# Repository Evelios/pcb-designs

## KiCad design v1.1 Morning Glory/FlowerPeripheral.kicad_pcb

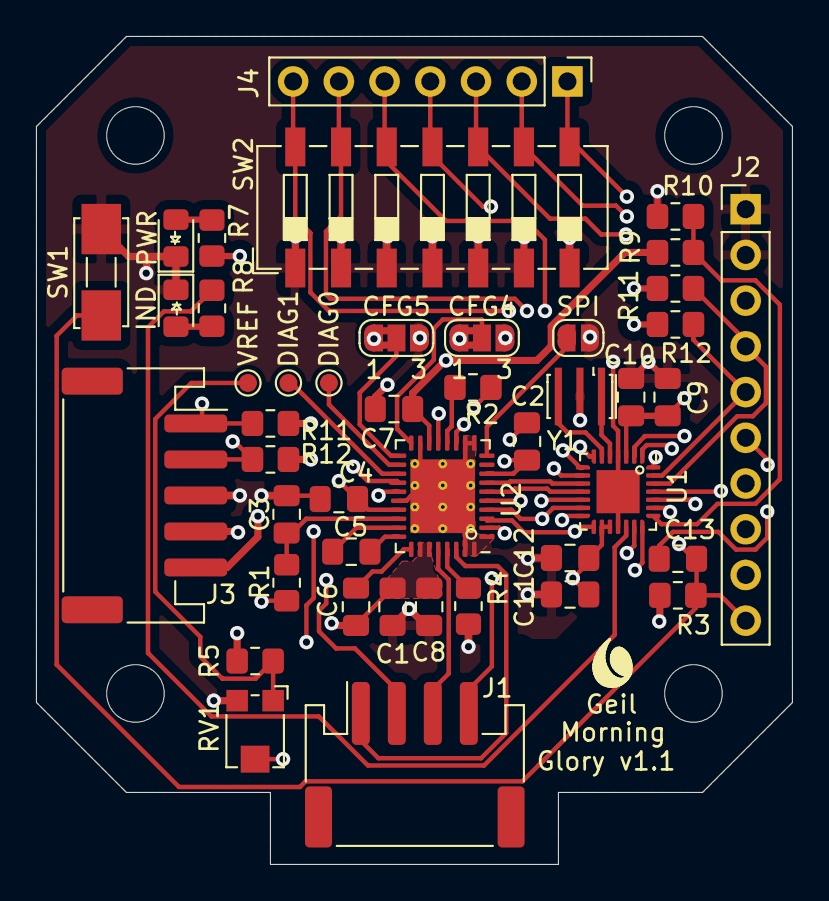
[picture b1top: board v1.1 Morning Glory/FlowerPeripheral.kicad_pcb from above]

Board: 4 copper layers, 42.0 x 46.0 mm, 45 parts (0 on the bottom side), 46 nets.

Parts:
C1, C2, C6, C7, C10, C11: 100n/50V; C_0805_2012Metric_Pad1.18x1.45mm_HandSolder
C3: 470n/10V; C_0805_2012Metric_Pad1.18x1.45mm_HandSolder
C4: 4u7/10v; C_0805_2012Metric_Pad1.18x1.45mm_HandSolder
C5: 22n/50V; C_0805_2012Metric_Pad1.18x1.45mm_HandSolder
C8: 1u/50V; C_0805_2012Metric_Pad1.18x1.45mm_HandSolder
C9: 10u; C_0805_2012Metric_Pad1.18x1.45mm_HandSolder
C12: 0.1u; C_0805_2012Metric_Pad1.18x1.45mm_HandSolder
C13: 100nF/50V; C_0805_2012Metric_Pad1.18x1.45mm_HandSolder
D2: PWR; LED_0805_2012Metric_Pad1.15x1.40mm_HandSolder_WithDirection
D3: IND; LED_0805_2012Metric_Pad1.15x1.40mm_HandSolder_WithDirection
H1: Nema17; Nema 17
J1: Motor Connector; JST_PH_S4B-PH-SM4-TB_1x04-1MP_P2.00mm_Horizontal
J2: Male Connector 10 Pin; PinHeader_1x10_P2.54mm_Vertical
J3: JST 5 Pin; JST_PH_S5B-PH-SM4-TB_1x05-1MP_P2.00mm_Horizontal
J4: Conn_01x07; PinHeader_1x07_P2.54mm_Vertical
J5: DIAG0; TestPoint_Pad_D1.0mm
J6: DIAG1; TestPoint_Pad_D1.0mm
J7: VREF; TestPoint_Pad_D1.0mm
JP1: SPI; SolderJumper-2_P1.3mm_Open_RoundedPad1.0x1.5mm
JP2: CFG4; SolderJumper-3_P1.3mm_Bridged2Bar12_RoundedPad1.0x1.5mm_Num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
JP3: CFG5; SolderJumper-3_P1.3mm_Bridged2Bar12_RoundedPad1.0x1.5mm_Num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
R1: 2R2; R_0805_2012Metric_Pad1.20x1.40mm_HandSolder
R2, R4: R0805/0R11; R_0805_2012Metric_Pad1.20x1.40mm_HandSolder
R3, R11, R11#2, R12, R12#2: 10K; R_0805_2012Metric_Pad1.20x1.40mm_HandSolder
R5: 20K; R_0805_2012Metric_Pad1.20x1.40mm_HandSolder
R7, R8: 150Ω; R_0805_2012Metric_Pad1.20x1.40mm_HandSolder
R9: 1M; R_0805_2012Metric_Pad1.20x1.40mm_HandSolder
R10: 100K; R_0805_2012Metric_Pad1.20x1.40mm_HandSolder
RV1: 20K; Potentiometer_Bourns_TC33X_Vertical
SW1: SW_SPST; SPST_FSM2JMTR
SW2: SW_DIP_x07; SW_DIP_SPSTx07_Slide_6.7x19.34mm_W6.73mm_P2.54mm_LowProfile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
U1: ATmega328P-PU; QFN-28-1EP_4x4mm_P0.45mm_EP2.4x2.4mm
U2: TMC2130-LA; QFN-36-1EP_5x6mm_P0.5mm_EP3.6x4.1mm_ThermalVias
Y1: 16Mhz; Resonator_SMD_muRata_CSTxExxV-3Pin_3.0x1.1mm_HandSoldering

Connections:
+5V: C2.1, C4.2, C9.1, C10.1, C11.1, C12.1, J2.3, J3.4, JP2.3, JP3.1, R1.1, R3.2, R5.2, R7.1, R11.1, R11#2.1, R12.1, R12#2.1, U1.3, U1.16, U1.17, U2.8, U2.25
+12V: C1.1, C6.1, C7.1, C8.1, J3.5, R9.1, U2.16, U2.30, U2.31
/CLKA: U1.5, Y1.1
/CLKB: U1.6, Y1.3
/DIR: U1.10, U2.7
/IND: R8.1, U1.19
/MISO: J2.8, U1.14, U2.5
/MOSI: J2.9, U1.13, U2.4
/P1: J4.7, SW2.14, U1.28
/P2: J4.6, SW2.13, U1.1
/P3: J4.5, SW2.12, U1.2
/P4: J4.4, SW2.11, U1.7
/P5: J4.3, SW2.10, U1.8
/P6: J4.2, SW2.9, U1.20
/P7: J4.1, SW2.8, U1.21
/RESET: C13.2, J2.10, R3.1, SW1.2, U1.25
/RX: J2.4, R11#2.2, U1.26
/SCK: J2.7, U1.15, U2.3
/SCL: J3.2, R12.2, U1.24
/SDA: J3.1, R11.2, U1.23
/SS: U1.12, U2.2
/STEP: U1.11, U2.6
/TMC2130_silentstepstick_v11/CFG4: JP2.2, U2.18
/TMC2130_silentstepstick_v11/CFG5: JP3.2, U2.19
/TMC2130_silentstepstick_v11/EN: U1.9, U2.22
/TMC2130_silentstepstick_v11/MA1: J1.1, U2.34
/TMC2130_silentstepstick_v11/MA2: J1.3, U2.32
/TMC2130_silentstepstick_v11/MB1: J1.4, U2.13
/TMC2130_silentstepstick_v11/MB2: J1.2, U2.15
/TX: J2.5, R12#2.2, U1.27
/VM_REF: R9.2, R10.1, U1.22
GND: C1.2, C2.2, C3.1, C4.1, C7.2, C8.2, C9.2, C10.2, C11.2, C12.2, D2.1, D3.1, J2.1, J2.2, J3.3, JP1.1, JP2.1, JP3.3, R2.2, R4.2, R10.2, RV1.3, SW1.1, SW2.1, SW2.2, SW2.3, SW2.4, SW2.5, SW2.6, SW2.7, U1.4, U1.18, U1.29, U2.1, U2.11, U2.12, U2.17, U2.24, U2.35, U2.36, U2.37, Y1.2
unnamed: C3.2, R1.2, U2.26
unnamed: C5.1, U2.28
unnamed: C5.2, U2.27
unnamed: C6.2, U2.29
unnamed: C13.1, J2.6
unnamed: D2.2, R7.2
unnamed: D3.2, R8.2
unnamed: J5.1, U2.20
unnamed: J6.1, U2.21
unnamed: J7.1, R5.1, RV1.1
unnamed: JP1.2, U2.10
unnamed: R2.1, U2.14
unnamed: R4.1, U2.33
unnamed: RV1.2, U2.23

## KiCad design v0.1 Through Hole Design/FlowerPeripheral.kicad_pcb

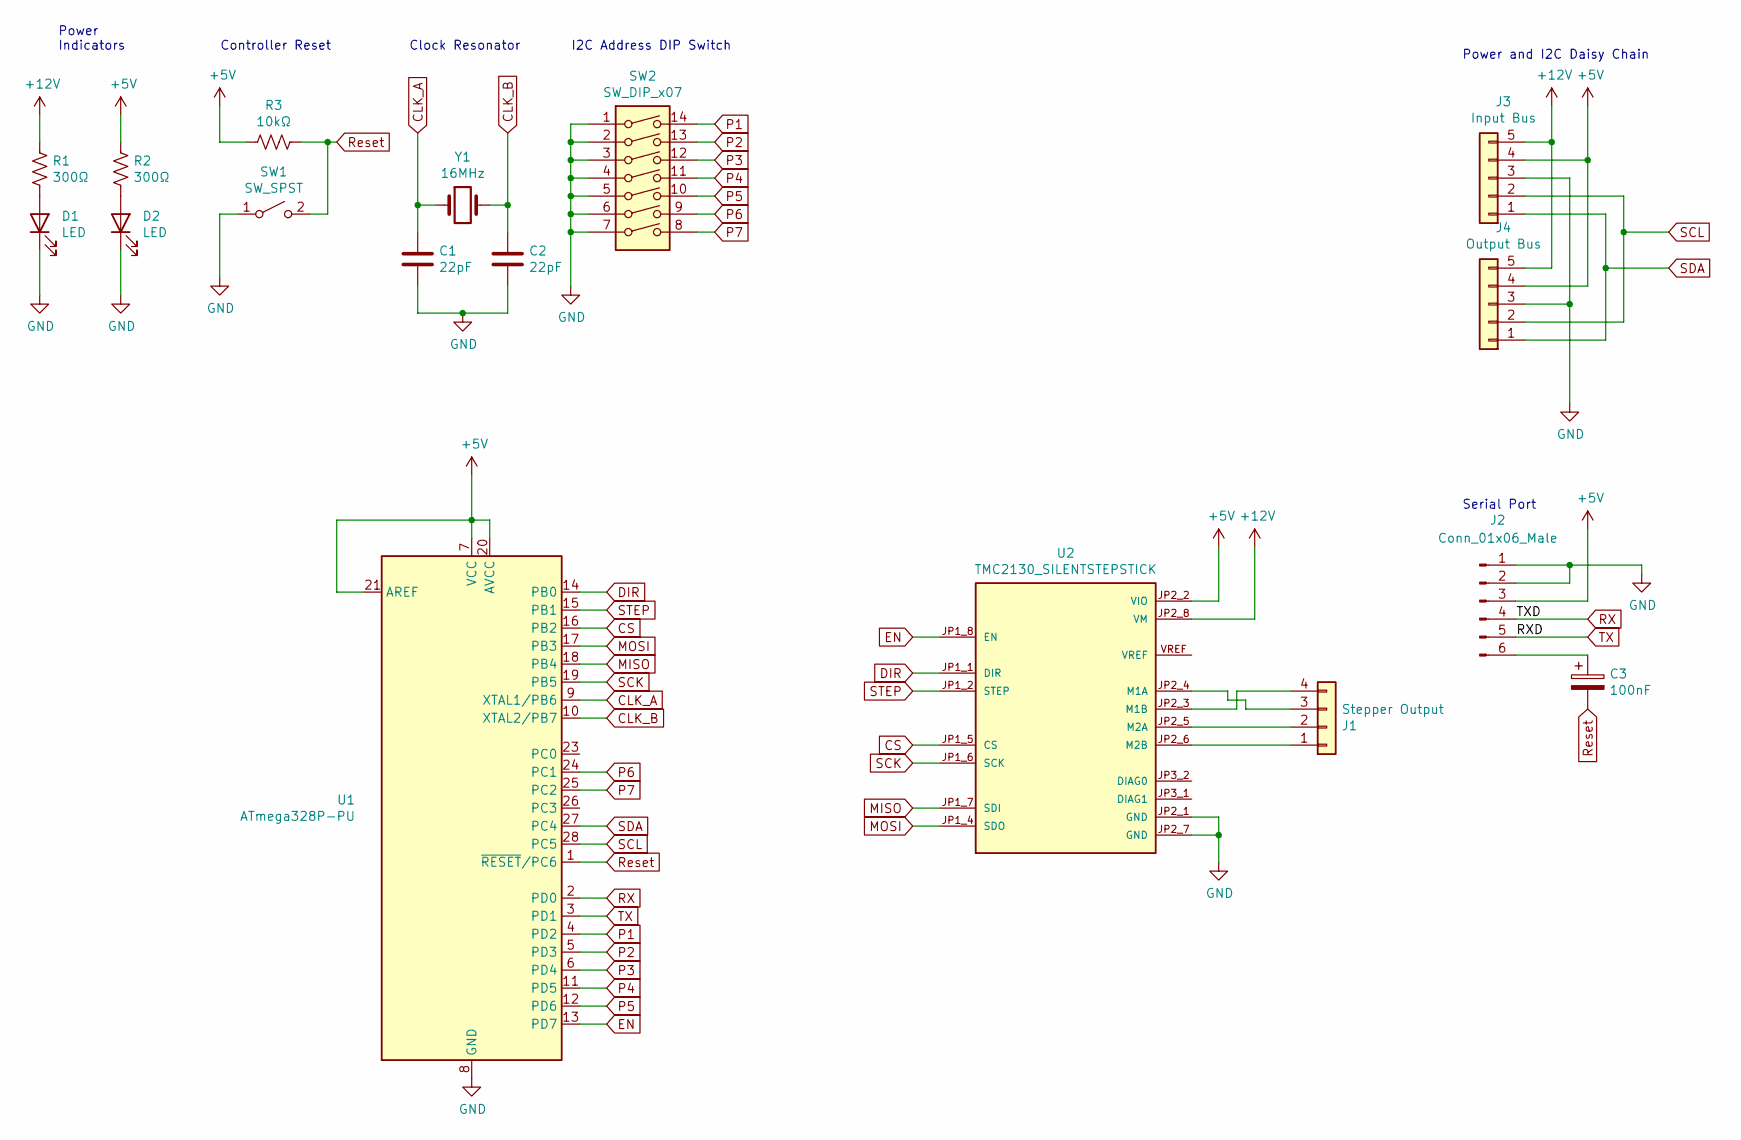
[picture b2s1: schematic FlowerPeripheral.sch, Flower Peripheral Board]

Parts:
C1, C2: 22pF; C_Disc_D5.0mm_W2.5mm_P2.50mm
C3: 100nF; CP_Radial_D4.0mm_P1.50mm
D1, D2: LED; LED_D3.0mm
J1: Stepper Output; JST_XH_B4B-XH-A_1x04_P2.50mm_Vertical
J2: Conn_01x06_Male; PinHeader_1x06_P2.54mm_Vertical
J3: Input Bus; JST_XH_B5B-XH-A_1x05_P2.50mm_Vertical
J4: Output Bus; JST_XH_B5B-XH-A_1x05_P2.50mm_Vertical
R1, R2: 300Ω; R_Axial_DIN0207_L6.3mm_D2.5mm_P10.16mm_Horizontal
R3: 10kΩ; R_Axial_DIN0207_L6.3mm_D2.5mm_P10.16mm_Horizontal
SW1: SW_SPST; SW_PUSH_6mm_H5mm
SW2: SW_DIP_x07; SW_DIP_SPSTx07_Slide_9.78x19.96mm_W7.62mm_P2.54mm
U1: ATmega328P-PU; DIP-28_W7.62mm_Socket
U2: TMC2130_SILENTSTEPSTICK; MODULE_TMC2130_SILENTSTEPSTICK
Y1: 16MHz; Crystal_HC49-U_Vertical

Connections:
+5V: J2.3, J3.4, J4.4, R2.1, R3.2, U1.7 (VCC), U1.20 (AVCC), U1.21 (AREF), U2.JP2_2 (VIO)
+12V: J3.5, J4.5, R1.1, U2.JP2_8 (VM)
CLK_A: C1.2, U1.9 (XTAL1/PB6), Y1.1
CLK_B: C2.2, U1.10 (XTAL2/PB7), Y1.2
CS: U1.16 (PB2), U2.JP1_5 (CS)
DIR: U1.14 (PB0), U2.JP1_1 (DIR)
EN: U1.13 (PD7), U2.JP1_8 (EN)
GND: C1.1, C2.1, D1.1 (K), D2.1 (K), J2.1, J2.2, J3.3, J4.3, SW1.1 (A), SW2.1, SW2.2, SW2.3, SW2.4, SW2.5, SW2.6, SW2.7, U1.8 (GND), U1.22 (GND), U2.JP2_1 (GND), U2.JP2_7 (GND)
MISO: U1.18 (PB4), U2.JP1_7 (SDI)
MOSI: U1.17 (PB3), U2.JP1_4 (SDO)
unnamed: C3.1, J2.6
unnamed: D1.2 (A), R1.2
unnamed: D2.2 (A), R2.2
unnamed: J1.1, U2.JP2_6 (M2B)
unnamed: J1.2, U2.JP2_5 (M2A)
unnamed: J1.3, U2.JP2_4 (M1A)
unnamed: J1.4, U2.JP2_3 (M1B)
P1: SW2.14, U1.4 (PD2)
P2: SW2.13, U1.5 (PD3)
P3: SW2.12, U1.6 (PD4)
P4: SW2.11, U1.11 (PD5)
P5: SW2.10, U1.12 (PD6)
P6: SW2.9, U1.24 (PC1)
P7: SW2.8, U1.25 (PC2)
RX: J2.4, U1.2 (PD0)
Reset: C3.2, R3.1, SW1.2 (B), U1.1 (~RESET~/PC6)
SCK: U1.19 (PB5), U2.JP1_6 (SCK)
SCL: J3.2, J4.2, U1.28 (PC5)
SDA: J3.1, J4.1, U1.27 (PC4)
STEP: U1.15 (PB1), U2.JP1_2 (STEP)
TX: J2.5, U1.3 (PD1)
VmRef: U1.23 (PC0)

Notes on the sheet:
Power and I2C Daisy Chain
I2C Address DIP Switch
Power Indicators
Controller Reset
Clock Resonator
Serial Port

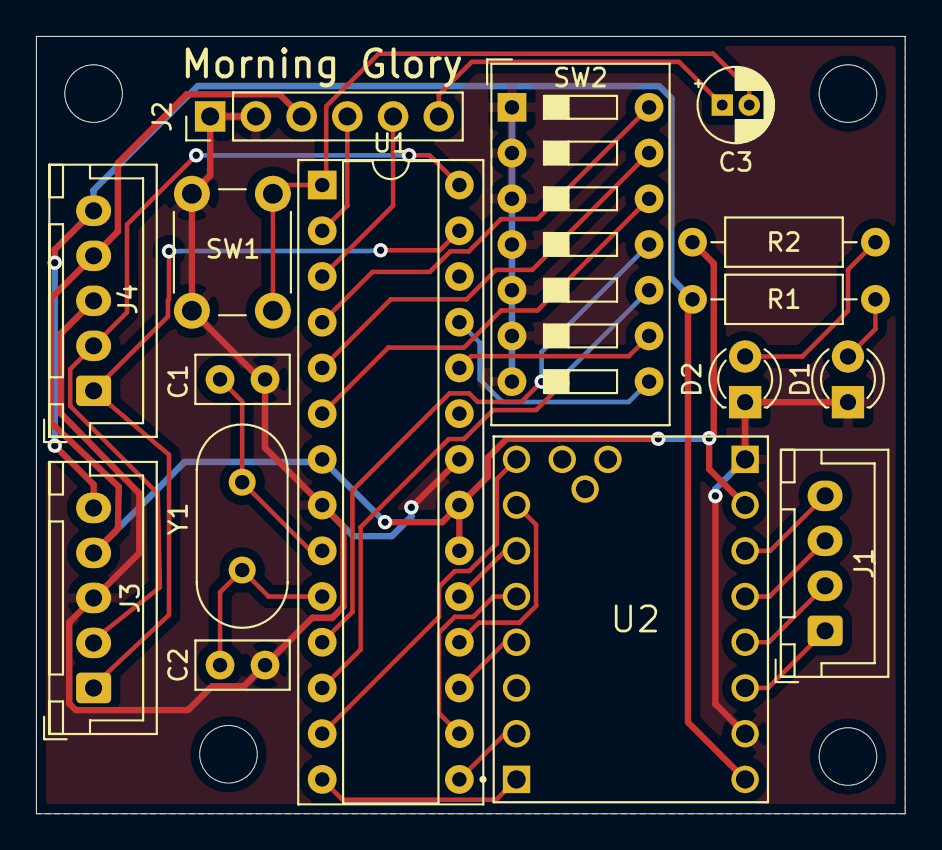
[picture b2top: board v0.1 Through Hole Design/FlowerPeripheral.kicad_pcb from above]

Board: 2 copper layers, 48.3 x 43.2 mm, 16 parts (0 on the bottom side), 31 nets.
